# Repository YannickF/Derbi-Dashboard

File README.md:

# Derbi-Dashboard
Tableau de bord pour moto 50 cm3 Derbi Senda (ou "équivalent)

Le circuit imprimé est le même pour les 3 parties, mais il y a eu quelques oublis
Compteur en 3 parties indépendantes, chacune avec un écran OLED 1.3''
- compteur de vitesse (capteure inductif fixé sur la fourche et qui détecte le passage des têtes de vis du disque de frein). Le compteur kilométrique est stockéen EEPROM. Le compteur journalier est remis à zéro à chaque démarrage)
- compte-tours : fil issu de l'alternateur, avec diode de redressement
- voyants : phares / clignotants / niveau huile (flotteur installé dans le réservoir) / température / essence (avec le capteur d'origine toujours cablé avec son ampoule car il ne fonctionne pas sans)

Oublis sur le circuit imprimé : 
- diviseur de tension par 2 (2 résistances de 10 kohms) sur le fil du feu de route

REMARQUE : le circuit électrique de la moto a été légèrement modifié
- le 12V alternatif (pour les feux) est maintenant sur le 12V issu du régulateur (l'éclairage est stable même au ralenti)
- le 12 alternatif est utilisé pour le compte-tour mais il est redressé simple alternance (une diode) avant d'aller au tableau de bord. Ce signal n'est pas assez propre au ralenti pour être exploité mais il va très bien pour le reste du temps.
- le capteur de niveau d'huile n'est plus utilisé, un flotteur (on/off) est installé sur le bocal (on peut sans doute s'inspirer de la gestion du niveau d'essence pour faire fonctionner le capteur d'origine)

FONCTIONNEMENT DES CAPTEURS
Les capteurs d'huile et d'essence ne fonctionnent pas sans l'ampoule.
Pour l'essence, j'ai mesuré les tensions suivantes (mesurées entre la masse et le point milieu)
  - réservoir vide : environ 5 à 6 V (ce qui laisse 6V pour l'ampoule qui brille un peu)
  - réservoir plein : environ 8 V (il reste donc 4V pour l'ampoule, ce qui est insuffisant)

+12V. ---------
              |
              |
            Ampoule
              |
              |----------------- mesure de la tension
              |
            Capteur
              |
              |
 0V -----------

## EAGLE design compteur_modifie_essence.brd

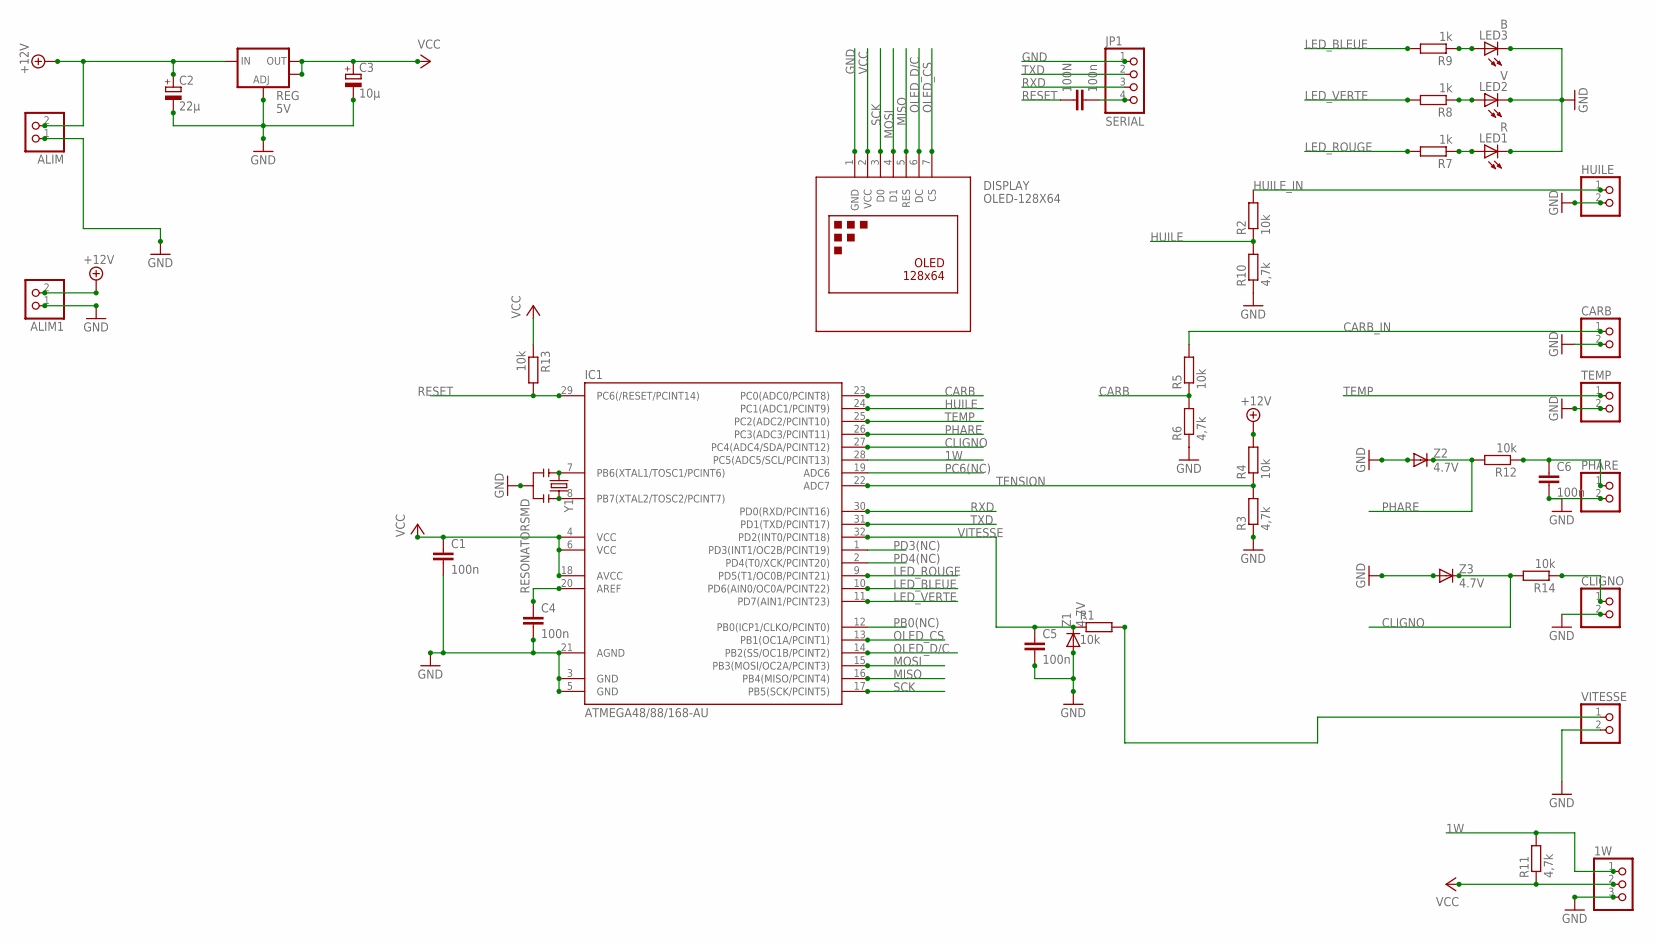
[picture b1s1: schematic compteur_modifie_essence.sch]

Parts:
1W: PINHD-1X3CB; 1X03-CLEANBIG
100N: 100n; C1206
ALIM, ALIM1: PINHD-1X2; 1X02
C1, C4, C5, C6: 100n; C1206
C2: 22µ; SMC_D
C3: 10µ; SMC_C
CARB: PINHD-1X2; 1X02
CLIGNO: PINHD-1X2; 1X02
DISPLAY: OLED-128X64; DISPLAY-OLED-128X64
HUILE: PINHD-1X2; 1X02
IC1: ATMEGA48/88/168-AU; TQFP32-08
JP1: SERIAL; 1X04_ROUND
LED1: R; LED5MM
LED2: V; LED5MM
LED3: B; LED5MM
PHARE: PINHD-1X2; 1X02
R1, R2, R4, R5, R12, R13, R14: 10k; R1206
R3, R6, R10, R11: 4,7k; R1206
R7, R8, R9: 1k; R1206
REG: 5V; SOT223
TEMP: PINHD-1X2; 1X02
VITESSE: PINHD-1X2; 1X02
Y1: RESONATORSMD; RESONATOR-SMD
Z1, Z2, Z3: 4.7V; SOD123

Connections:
1W: 1W.1, IC1.28 (PC5(ADC5/SCL/PCINT13)), R11.2
+12V: ALIM.2, ALIM1.2, C2.+, R4.2, REG.3 (IN)
AREF: C4.1, IC1.20 (AREF)
CARB: IC1.23 (PC0(ADC0/PCINT8)), R5.1, R6.2
CARB_IN: CARB.1, R5.2
CLIGNO: IC1.27 (PC4(ADC4/SDA/PCINT12)), R14.2, Z3.C
GND: 1W.3, ALIM.1, ALIM1.1, C1.2, C2.-, C3.-, C4.2, C5.2, C6.2, CARB.2, CLIGNO.2, DISPLAY.1 (GND), HUILE.2, IC1.3 (GND), IC1.5 (GND), IC1.21 (AGND), JP1.1, LED1.K (C), LED2.K (C), LED3.K (C), PHARE.2, R3.1, R6.1, R10.1, REG.1 (ADJ), TEMP.2, VITESSE.2, Y1.2, Z1.A, Z2.A, Z3.A
HUILE: IC1.24 (PC1(ADC1/PCINT9)), R2.1, R10.2
HUILE_IN: HUILE.1, R2.2
LED_BLEUE: IC1.10 (PD6(AIN0/OC0A/PCINT22)), R9.2
LED_ROUGE: IC1.9 (PD5(T1/OC0B/PCINT21)), R7.2
LED_VERTE: IC1.11 (PD7(AIN1/PCINT23)), R8.2
MISO: DISPLAY.5 (RES), IC1.16 (PB4(MISO/PCINT4))
MOSI: DISPLAY.4 (D1), IC1.15 (PB3(MOSI/OC2A/PCINT3))
unnamed: LED1.A, R7.1
unnamed: CLIGNO.1, R14.1
OLED_CS: DISPLAY.7 (CS), IC1.13 (PB1(OC1A/PCINT1))
OLED_D/C: DISPLAY.6 (DC), IC1.14 (PB2(SS/OC1B/PCINT2))
PB0(NC): IC1.12 (PB0(ICP1/CLKO/PCINT0))
PC6(NC): IC1.19 (ADC6)
PD3(NC): IC1.1 (PD3(INT1/OC2B/PCINT19))
PD4(NC): IC1.2 (PD4(T0/XCK/PCINT20))
PHARE: IC1.26 (PC3(ADC3/PCINT11)), R12.2, Z2.C
PHARE_IN: C6.1, PHARE.1, R12.1
R8: LED2.A, R8.1
R9: LED3.A, R9.1
RESET: 100N.1, IC1.29 (PC6(/RESET/PCINT14)), R13.2
RST: 100N.2, JP1.4
RXD: IC1.30 (PD0(RXD/PCINT16)), JP1.3
SCK: DISPLAY.3 (D0), IC1.17 (PB5(SCK/PCINT5))
TEMP: IC1.25 (PC2(ADC2/PCINT10)), TEMP.1
TENSION: IC1.22 (ADC7), R3.2, R4.1
TXD: IC1.31 (PD1(TXD/PCINT17)), JP1.2
VCC: 1W.2, C1.1, C3.+, DISPLAY.2 (VCC), IC1.4 (VCC), IC1.6 (VCC), IC1.18 (AVCC), R11.1, R13.1, REG.2 (OUT), REG.4 (OUT)
VITESSE: C5.1, IC1.32 (PD2(INT0/PCINT18)), R1.1, Z1.C
VITESS_IN: R1.2, VITESSE.1
XTAL1: IC1.7 (PB6(XTAL1/TOSC1/PCINT6)), Y1.1
XTAL2: IC1.8 (PB7(XTAL2/TOSC2/PCINT7)), Y1.3

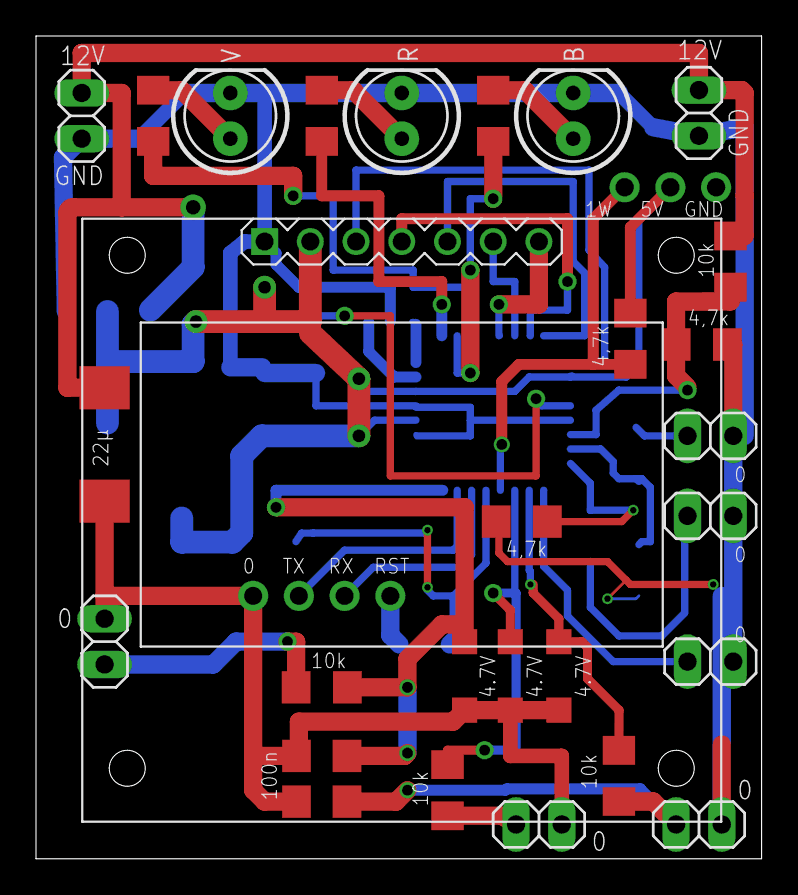
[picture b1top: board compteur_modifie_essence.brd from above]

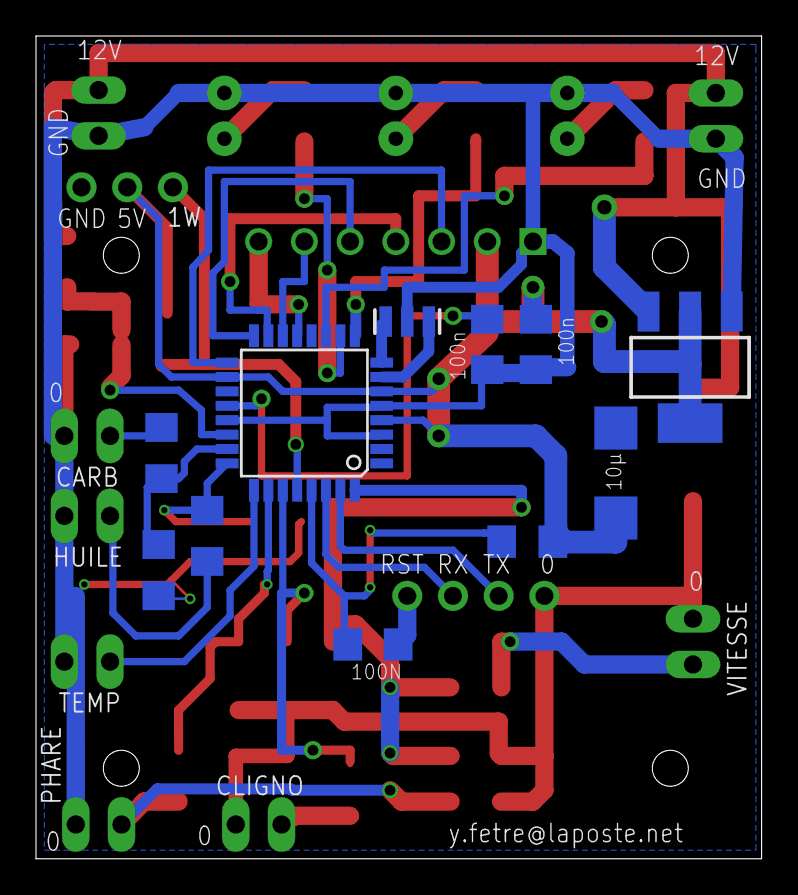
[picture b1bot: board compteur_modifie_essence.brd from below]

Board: 2 copper layers, 40.3 x 45.7 mm, 41 parts (12 on the bottom side), 34 nets.

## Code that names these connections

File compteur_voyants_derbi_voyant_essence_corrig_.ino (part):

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#include <OneWire.h>

#define MAX_TEMP 30 // temperature maximum pour le capteur 1W -> allumera le voyant si valeur dépassée
#define BATT_MAX 15.0  //tension maxi de la batterie
#define BATT_MIN 10.5  //tension mini de la batterie
#define ALLUME_ESSENCE_VIDE 550 // niveau du convertisseur Analogique numerique qui permet de basculer le voyant d'essence sur ON ou OFF
#define ALLUME_ESSENCE_PLEIN 750 // niveau d'essence PLEIN

#define pin_tension 7
#define pin_phare    A3
#define pin_cligno   A4
#define pin_essence  0
#define pin_huile    A1
#define pin_eau      A2
#define led_rouge    5
#define led_bleue    6
#define led_verte    7
#define BROCHE_ONEWIRE A5

//#define TEMPERATURE   //presence d'une sonde DS18B20
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

unsigned int temp=0;
float tension=0;
float temperature=0;
float essence_f=0; // valeur pour mesurer le "niveau" d'essence (le capteur associé à l'ampoule donne une tension en fonction du niveau, il faut donc utiliser le convertisseur analogique/numerique
signed int temperature_int=0;
boolean phare = false;
boolean cligno = false;
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#endif
  // configuration des broches en entrées / sorties
  analogReference(DEFAULT);
  pinMode(pin_tension,INPUT);
  pinMode(pin_phare,INPUT);
  pinMode(pin_cligno,INPUT);
  pinMode(pin_essence,INPUT);
  pinMode(pin_huile,INPUT_PULLUP);
  pinMode(pin_eau,INPUT_PULLUP);
  pinMode(led_rouge,OUTPUT);
  pinMode(led_bleue,OUTPUT);
  pinMode(led_verte,OUTPUT);

  // réduction de la résolution du DS18B20
  setResolution9bits();
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   //  lecture de la tension, on fait la moyenne sur 16 lectures
   temp=0;
   for (char i=0;i<=15;i++) {
    temp+=analogRead(pin_tension);
   }
   tension=(float) (temp / 16)  ;
   tension = tension* 0.015272;  // c'est le coefficient du convertisseur ADC
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  Serial.println();
 #endif
  // lecture des états des broches
  phare=digitalRead(pin_phare);
  cligno=digitalRead(pin_cligno);
  //essence=!digitalRead(pin_essence);
  huile=!digitalRead(pin_huile);
  capt_eau=!digitalRead(pin_eau);

  // TEST pour éviter les déclenchement intempestifs des alertes
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

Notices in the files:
parts and their libraries:
SparkFun: Licensing: CC v3.0 Share-Alike You are welcome to use this library for commercial purposes.
microbuilder: This work is placed in the public domain, and may be freely used for commercial and non-commercial work with the following conditions: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
